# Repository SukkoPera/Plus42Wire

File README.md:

# Plus42Wire
Plus42Wire is an I<sup>2</sup>C (Inter-Integrated Circuit, sometimes known as *2-Wire*) interface for the Commodore 16, 116 and Plus/4.

## Summary
I<sup>2</sup>C is a standard bus that is widely used for attaching lower-speed peripherals to processors, such as temperature/humidity/pressure sensors, real-time clocks, accelerometers, EEPROMs, ADCs and many more.

Plus42Wire is based on the PCF8584 chips by Philips/NXP, featuring both master and slave capabilities and communication speeds up to 90 kHz.

The board features both 5V and 3.3V bus connectors with different pinouts for maximum compatibility with devices and has built-in slots for an EEPROM and a real-time clock (RTC). Address decoding is performed by a GAL for easy reconfigurability (both GAL20 and GAL22 are supported).

## Assembly
The PCF8584 and all the other chips can all be bought supercheap on AliExpress & similar sites. There are only a couple of other components, making this board very affordable to build for everyone.

Be careful with the Q1/Q2 MOSFETs: these **MUST** be TN2106, get them from a reputable supplier. You can skip them if you are only interested in the 5V bus.

JP1 sets the built-in EEPROM to read-only mode when closed.

JP2 grounds pin 1 of the oscillator: most oscillators don't need this, so leave it open unless the datasheet of your oscillator says differently.

JP3/4/5 control the I<sup>2</sup>C address of the built-in EEPROM: most EEPROMs respond to 0x50 by default, but this address can be altered through these jumpers. Set them all to 0 to use the default.

JP6 connects the PCF8584 IRQ signal to the system IRQ signal: these two work differently so you **MUST** leave this jumper open. It is only provided for experimentation.

The battery is only needed by the RTC so that it keeps time while the board is unplugged. Speaking of the RTC, be careful if you get these from China as some of them just don't work at all.

Many different EEPROM chips are supported in the built-in slot: just make sure that the pinout matches and adapt your software.

## Programming
The board is generic and can be used for a multitude of purposes, but in all cases you will have to write some software on the computer side in order to interact with the devices.

The board exposes the two PCF8584 registers at $FE04/5. Interaction with these registers is a bit tricky and requires careful examination of the [datasheet](doc/PCF8584.pdf).

Some example code for interaction with the board, RTC and EEPROM is provided on the [Wiki](https://github.com/SukkoPera/Plus42Wire/wiki).

## Releases
If you want to get this board produced, you are recommended to get [the latest release](https://github.com/SukkoPera/Plus42Wire/releases) rather than the current git version, as the latter might be under development and is not guaranteed to be working.

Every release is accompanied by its Bill Of Materials (BOM) file and any relevant notes about it, which you are recommended to read carefully.

## License
The Plus42Wire documentation, including the design itself, is copyright &copy; SukkoPera 2024 and is licensed under the [Creative Commons Attribution-NonCommercial-ShareAlike 4.0 International License](https://creativecommons.org/licenses/by-nc-sa/4.0/).

This documentation is distributed *as is* and WITHOUT ANY EXPRESS OR IMPLIED WARRANTIES whatsoever with respect to its functionality, operability or use, including, without limitation, any implied warranties OF MERCHANTABILITY, SATISFACTORY QUALITY, FITNESS FOR A PARTICULAR PURPOSE or infringement. We expressly disclaim any liability whatsoever for any direct, indirect, consequential, incidental or special damages, including, without limitation, lost revenues, lost profits, losses resulting from business interruption or loss of data, regardless of the form of action or legal theory under which the liability may be asserted, even if advised of the possibility or likelihood of such damages.

## Support the Project
If you want to get some boards manufactured, you can get them from PCBWay through this link:

You get my gratitude and cheap, professionally-made and good quality PCBs, I get some credit that will help with this and [other projects](https://www.pcbway.com/project/member/shareproject/?bmbid=41100). You won't even have to worry about the various PCB options, it's all pre-configured for you!

Also, if you still have to register, [you can use this link](https://www.pcbway.com/setinvite.aspx?inviteid=41100) to get some bonus initial credit (and yield me some more).

You can also buy me a coffee if you want:

## Thanks
* Chequered Ink for the [Helicopta](https://www.fontspace.com/helicopta-font-f27740) font used in the logo.

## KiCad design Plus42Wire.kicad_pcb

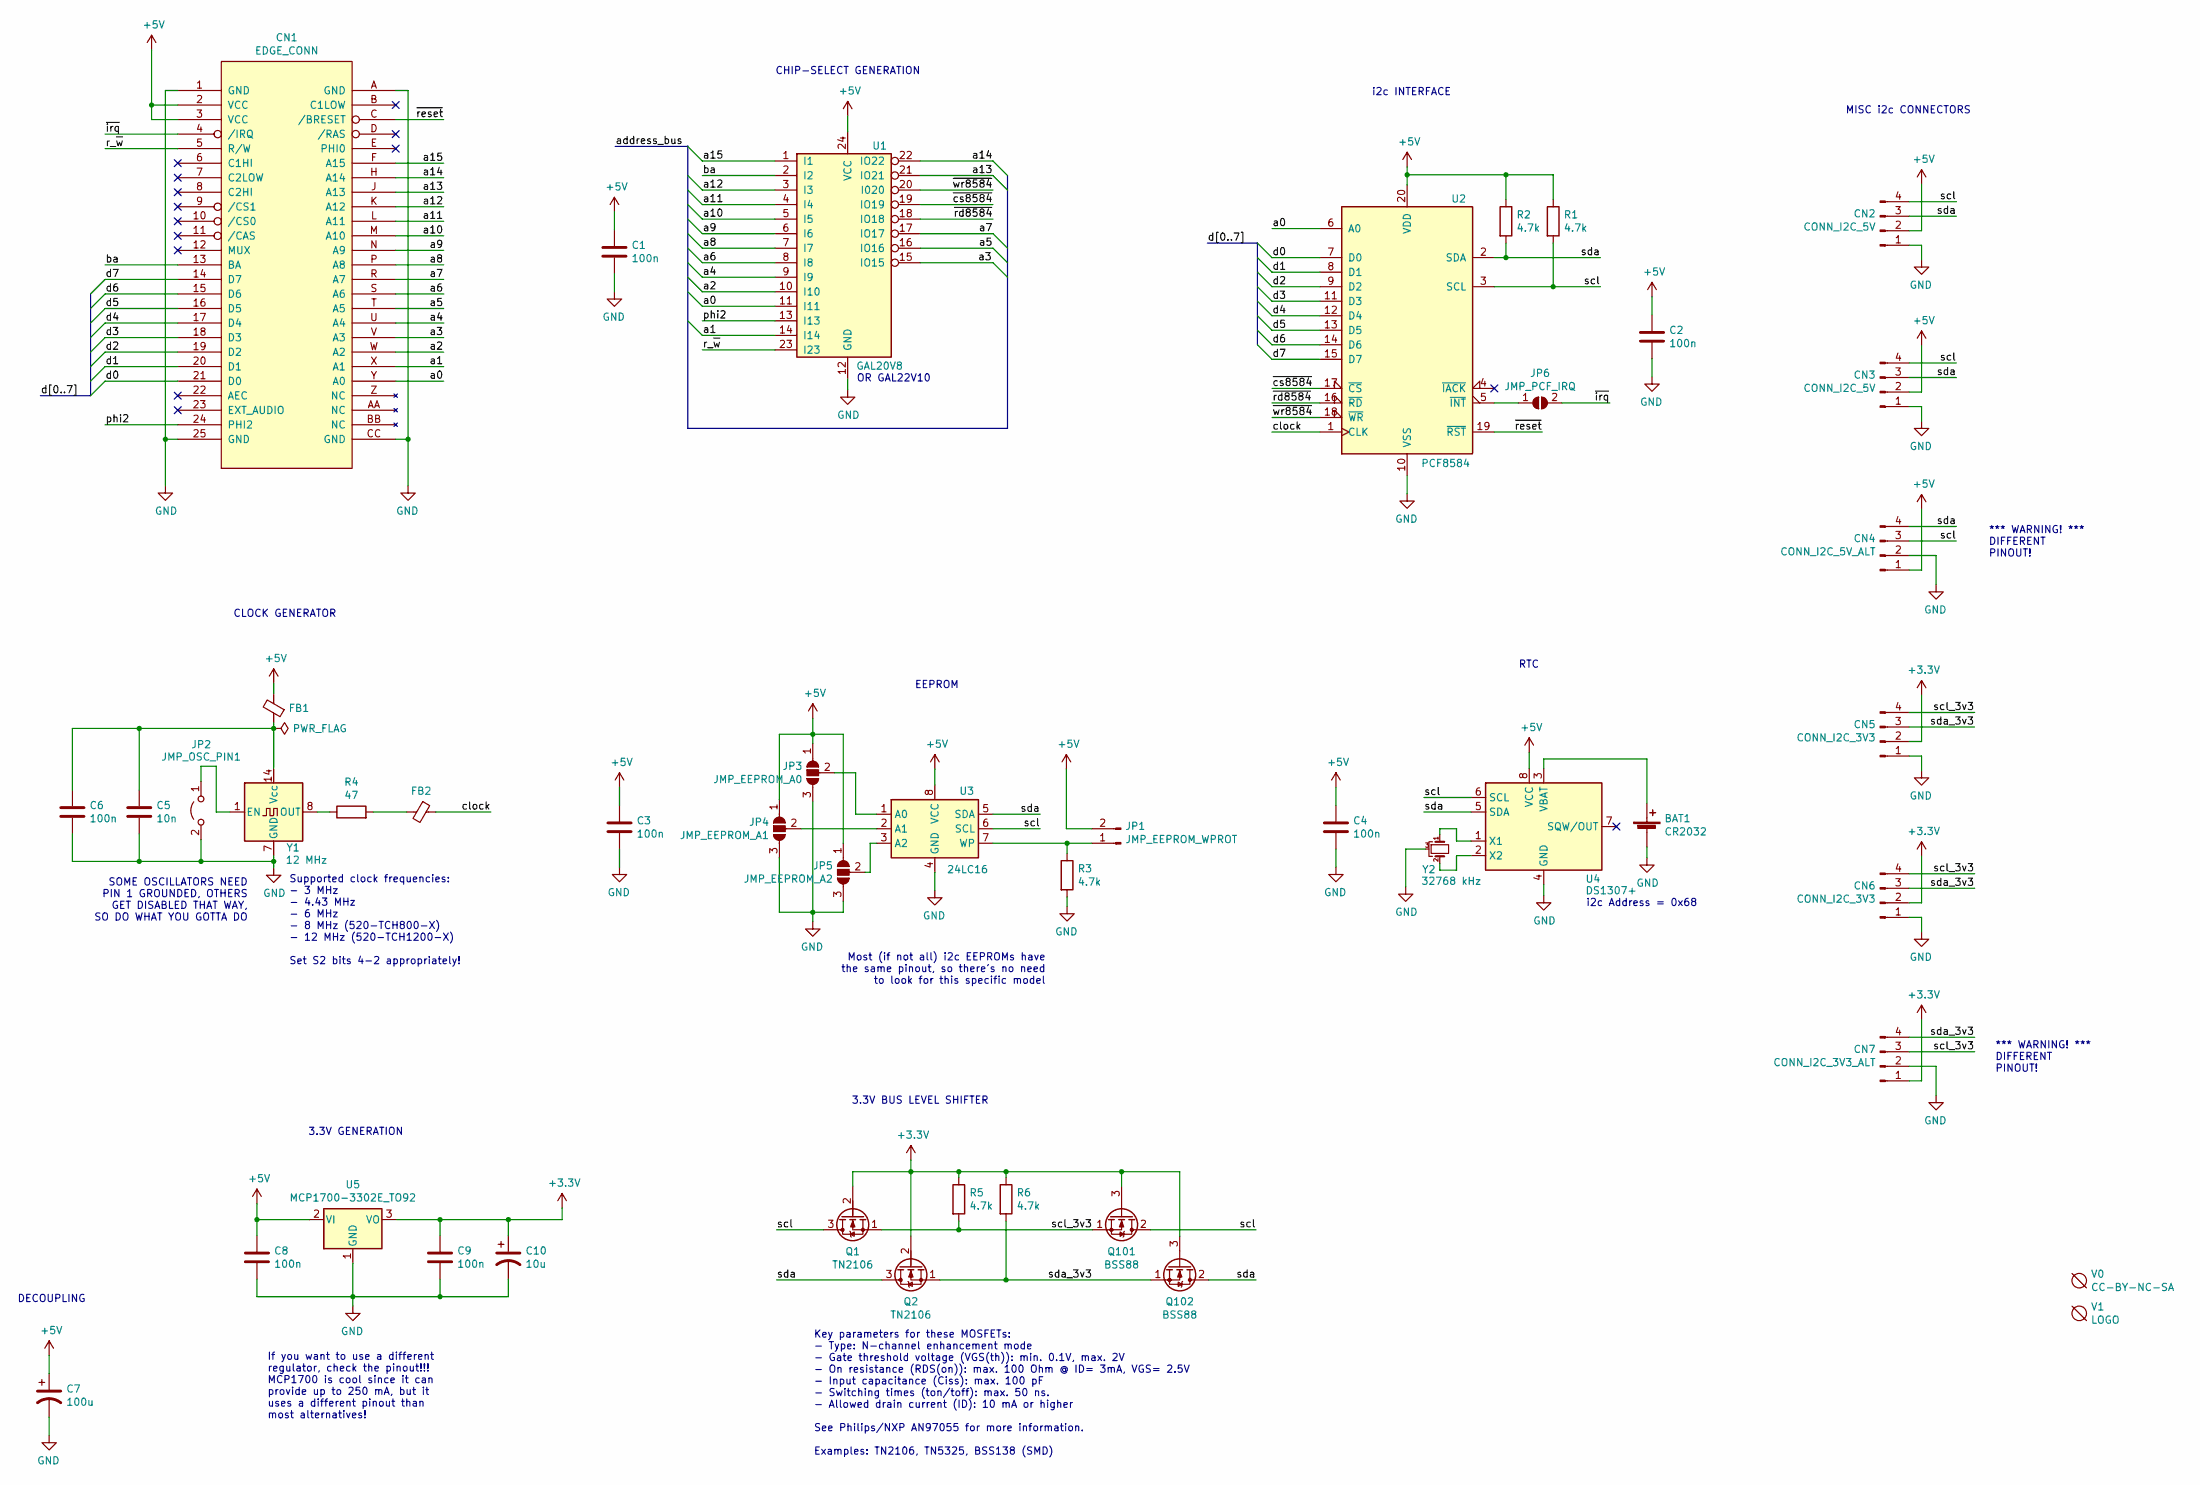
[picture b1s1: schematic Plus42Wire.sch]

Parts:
BAT1: CR2032; Battery_Holder_Coin_2032_BS-7
C1, C2, C3, C4, C6, C8, C9: 100n; C_Disc_D7.0mm_W2.5mm_P5.00mm; MouserPN 810-FG28X7R1H104KNT0
C5: 10n; C_Disc_D7.0mm_W2.5mm_P5.00mm
C7: 100u; CP_Radial_D6.3mm_P2.50mm; MouserPN 710-860020573008
C10: 10u; CP_Radial_D5.0mm_P2.00mm; MouserPN 710-860020573008
CN1: EDGE_CONN; C16_Cart_Conn
CN2, CN3: CONN_I2C_5V; PinHeader_1x04_P2.54mm_Vertical
CN4: CONN_I2C_5V_ALT; PinHeader_1x04_P2.54mm_Vertical
CN5, CN6: CONN_I2C_3V3; PinHeader_1x04_P2.54mm_Vertical
CN7: CONN_I2C_3V3_ALT; PinHeader_1x04_P2.54mm_Vertical
FB1, FB2: FERRITE; L_Radial_D6.0mm_P4.00mm; MouserPN 875-28C0236-0EW-10
JP1: JMP_EEPROM_WPROT; PinHeader_1x02_P2.54mm_Vertical
JP2: JMP_OSC_PIN1; SolderJumper-2_P1.3mm_Open_RoundedPad1.0x1.5mm
JP3: JMP_EEPROM_A0; SolderJumper-3_P1.3mm_Open_RoundedPad1.0x1.5mm
JP4: JMP_EEPROM_A1; SolderJumper-3_P1.3mm_Open_RoundedPad1.0x1.5mm
JP5: JMP_EEPROM_A2; SolderJumper-3_P1.3mm_Open_RoundedPad1.0x1.5mm
JP6: JMP_PCF_IRQ; SolderJumper-2_P1.3mm_Open_RoundedPad1.0x1.5mm
Q1, Q2: TN2106; TO-92L_HandSolder
Q101, Q102: BSS88; TO-92L_HandSolder
R1, R2, R3, R5, R6: 4.7k; R_Axial_DIN0207_L6.3mm_D2.5mm_P10.16mm_Horizontal
R4: 47; R_Axial_DIN0207_L6.3mm_D2.5mm_P10.16mm_Horizontal
U1: GAL20V8; DIP-24_W7.62mm_Socket_LongPads; MouserPN 556-AF22LV10CQZ-30PU
U2: PCF8584; DIP-20_W7.62mm_Socket_LongPads
U3: 24LC16; DIP-8_W7.62mm_Socket_LongPads
U4: DS1307+; DIP-8_W7.62mm_Socket_LongPads; MouserPN 700-DS1307N
U5: MCP1700-3302E_TO92; TO-92L_HandSolder; MouserPN 579-MCP1700-3302E/TO
V0: CC-BY-NC-SA; cc_by_nc_sa
V1: LOGO; Logo
Y1: 12 MHz; Oscillator_DIP-8+14; MouserPN 774-MXO45-3C-16.0
Y2: 32768 kHz; Crystal_AT310_D3.0mm_L10.0mm_Horizontal_1EP_style2

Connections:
+3V3: C9.1, C10.1, CN5.2, CN6.2, CN7.1, Q1.2 (G), Q2.2 (G), Q101.3 (G), Q102.3 (G), R5.1, R6.1, U5.3 (VO)
+5V: C1.1, C2.1, C3.1, C4.1, C7.1, C8.1, CN1.2 (VCC), CN1.3 (VCC), CN2.2, CN3.2, CN4.1, FB1.2, JP1.2, JP3.1 (A), JP4.1 (A), JP5.1 (A), R1.1, R2.1, U1.24 (VCC), U2.20 (VDD), U3.8 (VCC), U4.8 (VCC), U5.2 (VI)
/a0: CN1.Y (A0), U1.11 (I11), U2.6 (A0)
/a1: CN1.X (A1), U1.14 (I14)
/a2: CN1.W (A2), U1.10 (I10)
/a3: CN1.V (A3), U1.15 (IO15)
/a4: CN1.U (A4), U1.9 (I9)
/a5: CN1.T (A5), U1.16 (IO16)
/a6: CN1.S (A6), U1.8 (I8)
/a7: CN1.R (A7), U1.17 (IO17)
/a8: CN1.P (A8), U1.7 (I7)
/a9: CN1.N (A9), U1.6 (I6)
/a10: CN1.M (A10), U1.5 (I5)
/a11: CN1.L (A11), U1.4 (I4)
/a12: CN1.K (A12), U1.3 (I3)
/a13: CN1.J (A13), U1.21 (IO21)
/a14: CN1.H (A14), U1.22 (IO22)
/a15: CN1.F (A15), U1.1 (I1)
/ba: CN1.13 (BA), U1.2 (I2)
/clock: FB2.1, U2.1 (CLK)
/d0: CN1.21 (D0), U2.7 (D0)
/d1: CN1.20 (D1), U2.8 (D1)
/d2: CN1.19 (D2), U2.9 (D2)
/d3: CN1.18 (D3), U2.11 (D3)
/d4: CN1.17 (D4), U2.12 (D4)
/d5: CN1.16 (D5), U2.13 (D5)
/d6: CN1.15 (D6), U2.14 (D6)
/d7: CN1.14 (D7), U2.15 (D7)
/phi2: CN1.24 (PHI2), U1.13 (I13)
/r_~w: CN1.5 (R/W), U1.23 (I23)
/scl: CN2.4, CN3.4, CN4.3, Q1.3 (D), Q101.2 (D), R1.2, U2.3 (SCL), U3.6 (SCL), U4.6 (SCL)
/scl_3v3: CN5.4, CN6.4, CN7.3, Q1.1 (S), Q101.1 (S), R5.2
/sda: CN2.3, CN3.3, CN4.4, Q2.3 (D), Q102.2 (D), R2.2, U2.2 (SDA), U3.5 (SDA), U4.5 (SDA)
/sda_3v3: CN5.3, CN6.3, CN7.4, Q2.1 (S), Q102.1 (S), R6.2
/~cs8584: U1.19 (IO19), U2.17 (~CS~)
/~irq: CN1.4 (/IRQ), JP6.2 (B)
/~rd8584: U1.18 (IO18), U2.16 (~RD~)
/~reset: CN1.C (/BRESET), U2.19 (~RST~)
/~wr8584: U1.20 (I020), U2.18 (~WR~)
GND: BAT1.2 (-), C1.2, C2.2, C3.2, C4.2, C5.2, C6.2, C7.2, C8.2, C9.2, C10.2, CN1.1 (GND), CN1.25 (GND), CN1.A (GND), CN1.CC (GND), CN2.1, CN3.1, CN4.2, CN5.1, CN6.1, CN7.2, JP2.2 (B), JP3.3 (B), JP4.3 (B), JP5.3 (B), R3.2, U1.12 (GND), U2.10 (VSS), U3.4 (GND), U4.4 (GND), U5.1 (GND), Y1.7 (GND), Y2.3
unnamed: BAT1.1 (+), U4.3 (VBAT)
unnamed: C5.1, C6.1, FB1.1, Y1.14 (Vcc)
unnamed: FB2.2, R4.2
unnamed: JP1.1, R3.1, U3.7 (WP)
unnamed: JP2.1 (A), Y1.1 (EN)
unnamed: JP3.2 (C), U3.1 (A0)
unnamed: JP4.2 (C), U3.2 (A1)
unnamed: JP5.2 (C), U3.3 (A2)
unnamed: JP6.1 (A), U2.5 (~INT~)
unnamed: R4.1, Y1.8 (OUT)
unnamed: U4.1 (X1), Y2.1
unnamed: U4.2 (X2), Y2.2

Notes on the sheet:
CHIP-SELECT GENERATION
OR GAL22V10
SOME OSCILLATORS NEED PIN 1 GROUNDED, OTHERS GET DISABLED THAT WAY, SO DO WHAT YOU GOTTA DO
CLOCK GENERATOR
Supported clock frequencies: - 3 MHz - 4.43 MHz - 6 MHz - 8 MHz (520-TCH800-X) - 12 MHz (520-TCH1200-X) Set S2 bits 4-2 appropriately!
DECOUPLING
Most (if not all) i2c EEPROMs have the same pinout, so there's no need to look for this specific model
i2c Address = 0x68
EEPROM
RTC
MISC i2c CONNECTORS
i2c INTERFACE
3.3V GENERATION
Key parameters for these MOSFETs: - Type: N-channel enhancement mode - Gate threshold voltage (VGS(th)): min. 0.1V, max. 2V - On resistance (RDS(on)): max. 100 Ohm @ ID= 3mA, VGS= 2.5V - Input capacitance (Ciss): max. 100 pF - Switching times (ton/toff): max. 50 ns. - Allowed drain current (ID): 10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
3.3V BUS LEVEL SHIFTER
If you want to use a different regulator, check the pinout!!! MCP1700 is cool since it can provide up to 250 mA, but it uses a different pinout than most alternatives!
*** WARNING! *** DIFFERENT PINOUT!

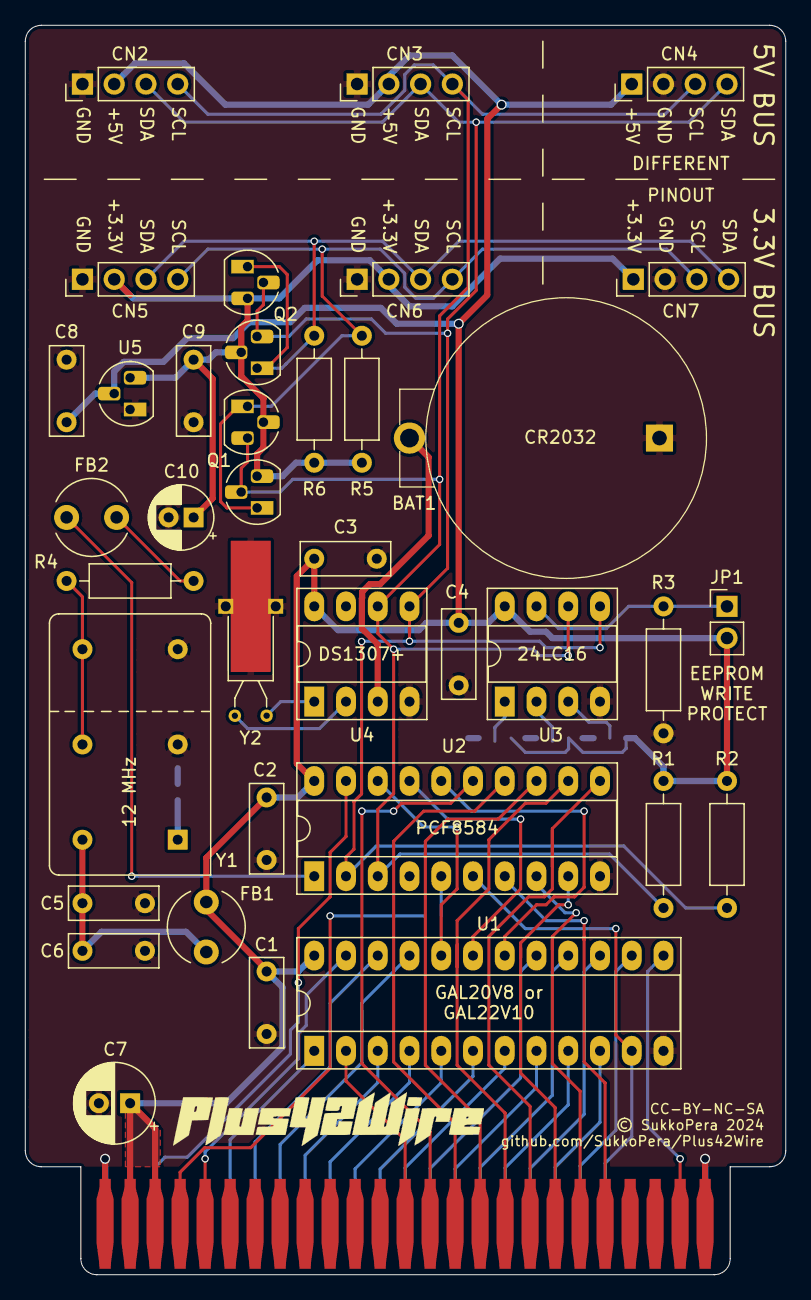
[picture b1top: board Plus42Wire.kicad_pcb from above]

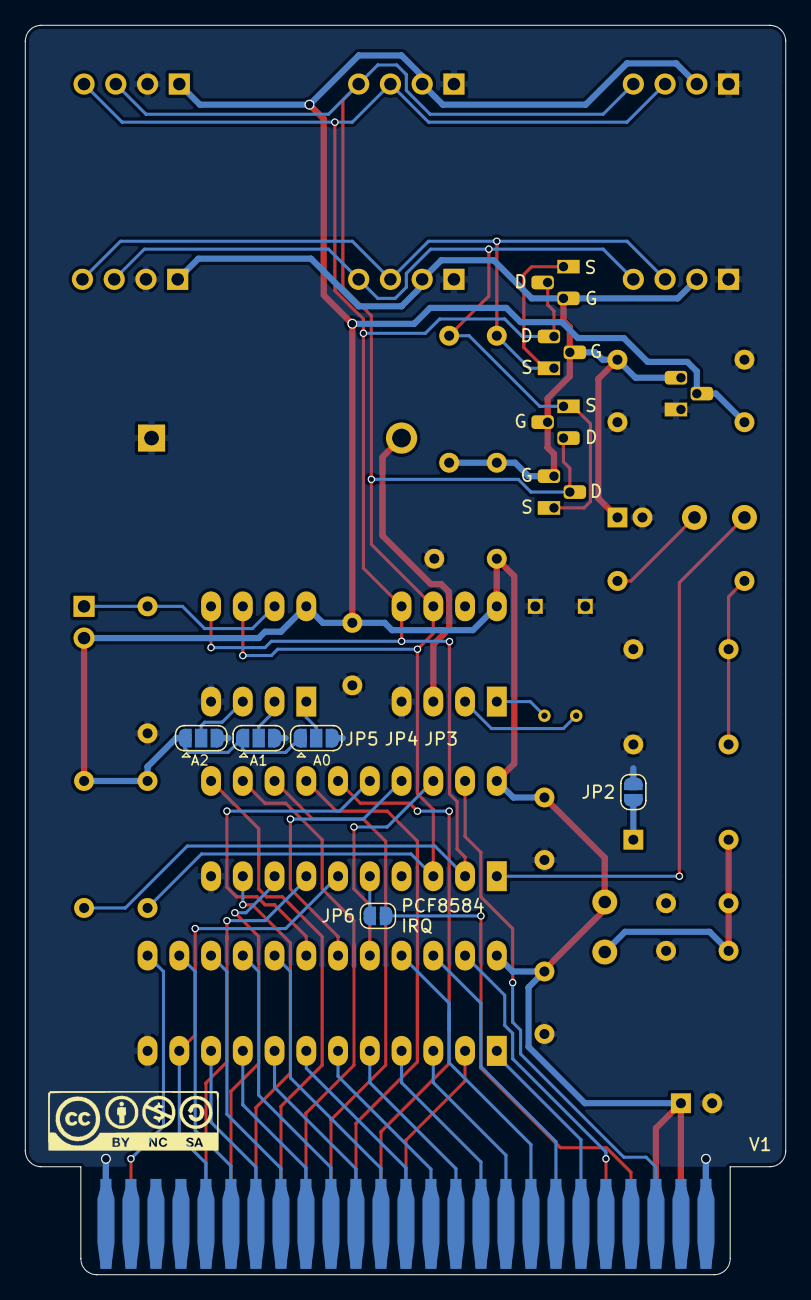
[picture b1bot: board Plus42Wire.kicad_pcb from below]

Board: 2 copper layers, 60.8 x 99.9 mm, 45 parts (6 on the bottom side), 52 nets.

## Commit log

2024-09-05 Initial version
2024-09-05 Add 3.3V bus
2024-09-05 Ready for V1rc1
2024-12-31 Add README
2024-12-31 Add GAL equations
2024-12-31 Add renders
2024-12-31 Update board link
2025-01-01 Add footprints for alternative MOSFETs
2026-02-13 Update coffee donation link and image
    Updated the coffee donation link with a new image.

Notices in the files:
Plus42Wire.kicad_pcb:
Licensed under CC BY-NC-SA 4.0
